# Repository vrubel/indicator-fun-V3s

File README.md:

# indicator-fun-V3s
Device "indicator.fun" implementation on the processor Allwinner V3s

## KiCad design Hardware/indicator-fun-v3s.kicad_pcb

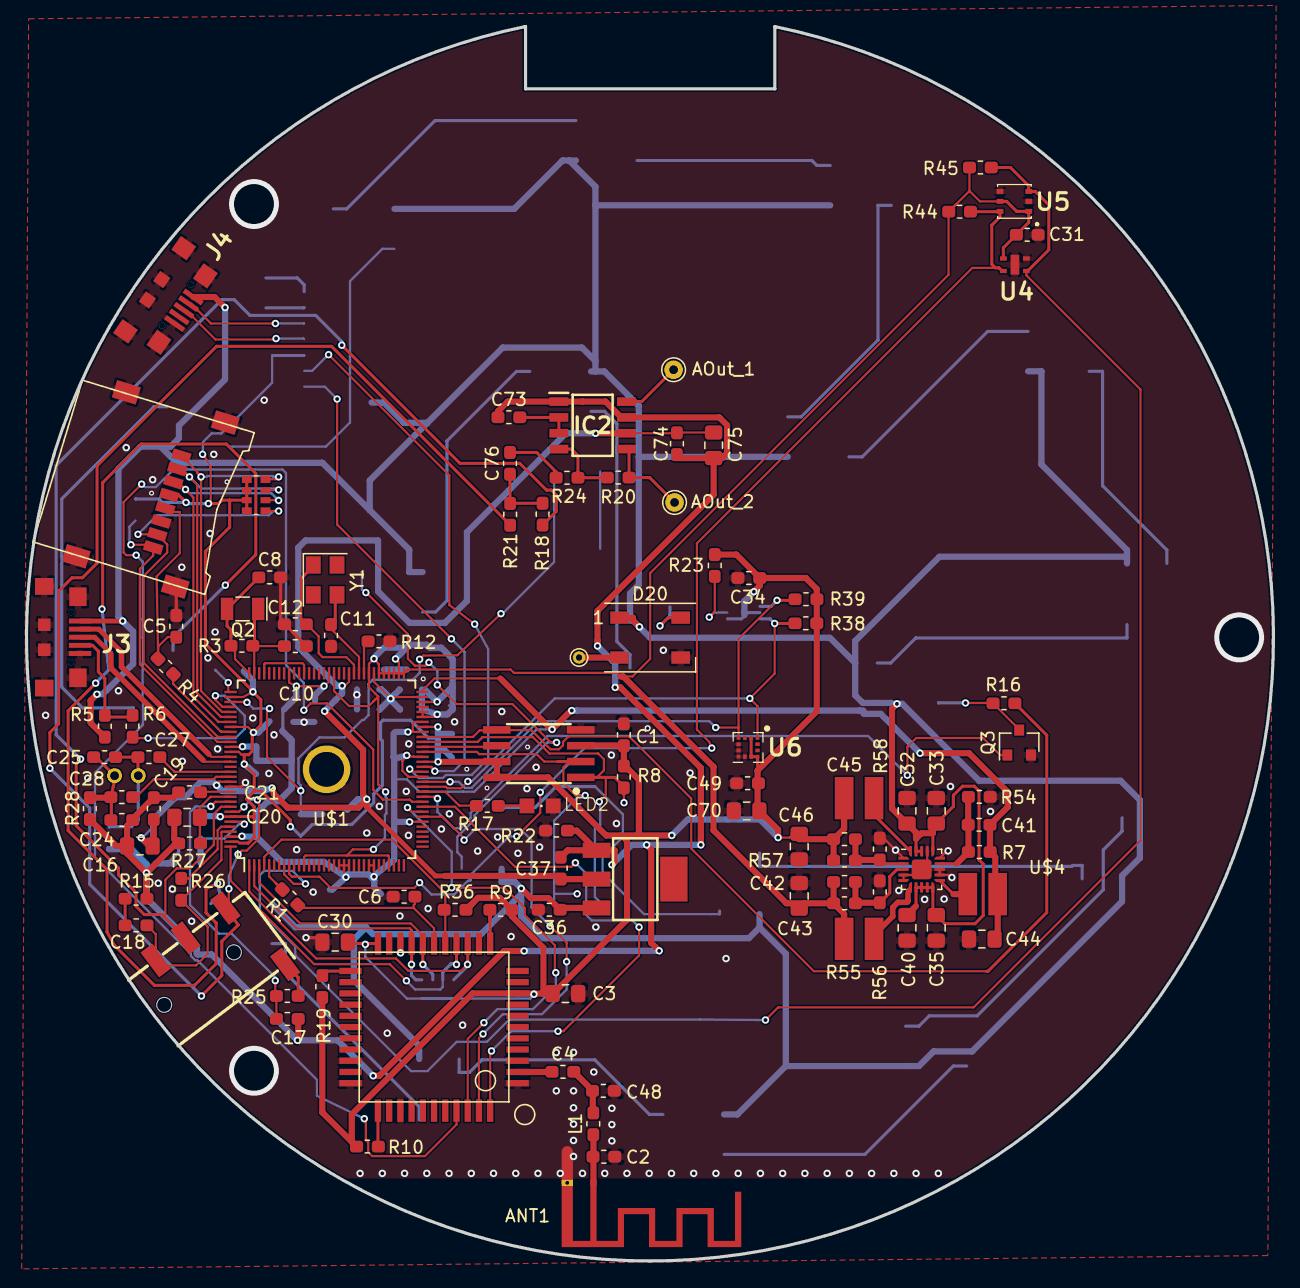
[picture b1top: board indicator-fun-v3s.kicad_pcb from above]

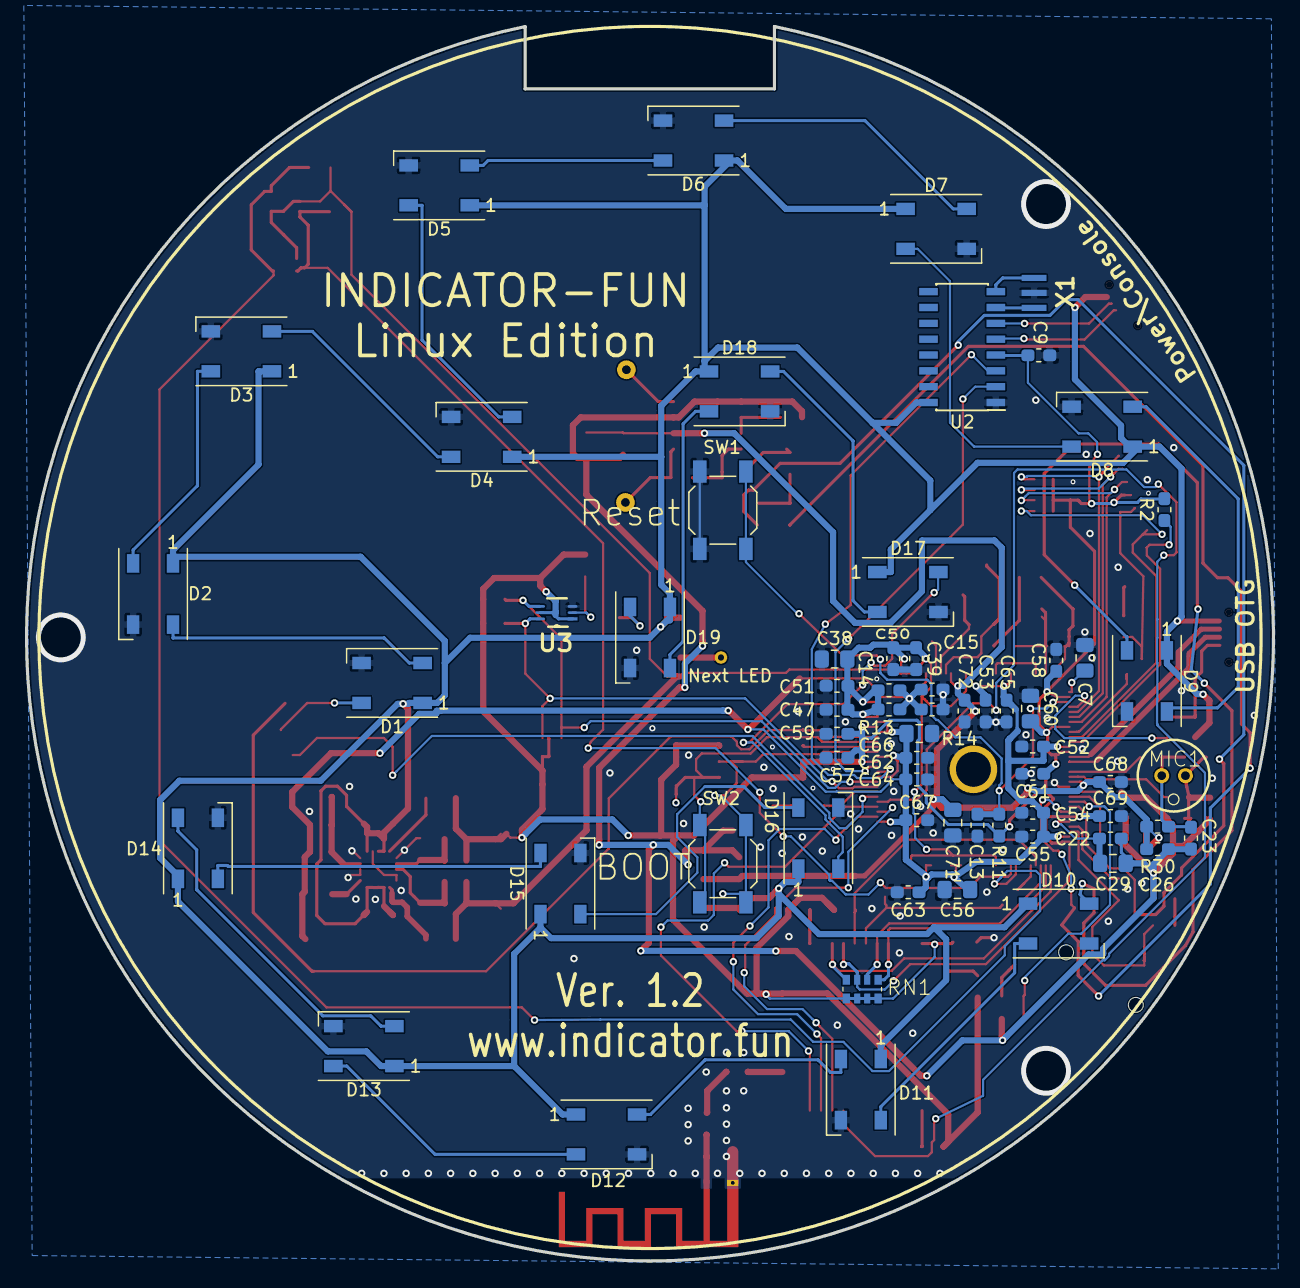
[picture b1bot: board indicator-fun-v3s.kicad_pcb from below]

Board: 2 copper layers, 100.0 x 99.0 mm, 168 parts (65 on the bottom side), 109 nets.

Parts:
ANT1: SWRA117D; Texas_SWRA117D_2.4GHz_Left
AOut_1: AOut_1; TestPoint_THTPad_D1.5mm_Drill0.7mm
AOut_2: AOut_2; TestPoint_THTPad_D1.5mm_Drill0.7mm
C1, C9, C14, C15, C18, C19, C22, C27, C28, C50, C51, C52, C53, C57, C58, C62, C63, C67, C68, C69, C72, C73, C74: 100nF; C_0603_1608Metric_Pad1.05x0.95mm_HandSolder
C2: 1pF; C_0603_1608Metric_Pad1.05x0.95mm_HandSolder
C3, C7, C16, C29, C30, C32, C33, C35, C38, C40, C43, C44, C46, C56, C60, C66, C71, C75: 10µF; C_0805_2012Metric_Pad1.15x1.40mm_HandSolder
C4: 10pF; C_0603_1608Metric_Pad1.05x0.95mm_HandSolder
C5, C6: 4.7pF; C_0603_1608Metric_Pad1.05x0.95mm_HandSolder
C8, C10, C11, C12, C41, C42, C45: 18pF; C_0603_1608Metric_Pad1.05x0.95mm_HandSolder
C13, C17, C21, C39, C47, C54, C55, C59, C61, C64, C65: 1µF; C_0603_1608Metric_Pad1.05x0.95mm_HandSolder
C20: 4.7µF; C_0805_2012Metric_Pad1.15x1.40mm_HandSolder
C23, C24, C26: 33pF; C_0603_1608Metric_Pad1.05x0.95mm_HandSolder
C25: 100pF; C_0603_1608Metric_Pad1.05x0.95mm_HandSolder
C31, C34, C49: 0.1uf; C_0603_1608Metric_Pad1.05x0.95mm_HandSolder
C36, C37: 100nf; C_0603_1608Metric_Pad1.05x0.95mm_HandSolder
C48: 1.2pF; C_0603_1608Metric_Pad1.05x0.95mm_HandSolder
C70: 22µF; C_0805_2012Metric_Pad1.15x1.40mm_HandSolder
C76: 0.22µF; C_0603_1608Metric_Pad1.05x0.95mm_HandSolder
D1, D2, D3, D4, D5, D6, D7, D8, D9, D10, D11, D12, D13, D14, D15, D16, D17, D18, D19, D20: WS2812B; LED_WS2812B_PLCC4_5.0x5.0mm_P3.2mm
IC1: LM1117; SOT223
IC2: MD8002A; SOIC127P600X175-8N
J1: TRANSFLASH-LOCK; TRANSFLASH-LOCK-SOCK
J2: AUDIO_JACK_SMD; AUDIO_JACK_3.5MM_TRRS_SMD_RA
J3: USB OTG; USB-B-Micro
J4: Power\Console; USB-B-Micro
L1: 2.2nH; L_0603_1608Metric_Pad1.05x0.95mm_HandSolder
L3, L4: 2,2µH; ODD-INDUCTOR
L5: 2.2µH; ODD-INDUCTOR
LED2: LEDCHIPLED_0805; CHIPLED_0805
MIC1: ELECTRET_MICROPHON-F6035AP; F6035AP
Q2: 32kHz; Crystal_SMD_MicroCrystal_CC7V-T1A-2Pin_3.2x1.5mm
Q3: BSS138; SOT-23
R1, R4: 33; R_0603_1608Metric_Pad1.05x0.95mm_HandSolder
R2, R11, R36: 47k; R_0603_1608Metric_Pad1.05x0.95mm_HandSolder
R3: 10M; R_0603_1608Metric_Pad1.05x0.95mm_HandSolder
R5, R9, R10, R56: 100k; R_0603_1608Metric_Pad1.05x0.95mm_HandSolder
R6, R17: 1k; R_0603_1608Metric_Pad1.05x0.95mm_HandSolder
R7, R54, R58: 150k; R_0603_1608Metric_Pad1.05x0.95mm_HandSolder
R8, R18, R19, R21, R38, R39, R44, R45: 10k; R_0603_1608Metric_Pad1.05x0.95mm_HandSolder
R12: 240 - 1%; R_0603_1608Metric_Pad1.05x0.95mm_HandSolder
R13, R14: 2k - 1%; R_0603_1608Metric_Pad1.05x0.95mm_HandSolder
R15: 22; R_0603_1608Metric_Pad1.05x0.95mm_HandSolder
R16: 300; R_0603_1608Metric_Pad1.05x0.95mm_HandSolder
R20: 68k; R_0603_1608Metric_Pad1.05x0.95mm_HandSolder
R22, R26: 0; R_0603_1608Metric_Pad1.05x0.95mm_HandSolder
R23: 10K; R_0603_1608Metric_Pad1.05x0.95mm_HandSolder
R24: 22k; R_0603_1608Metric_Pad1.05x0.95mm_HandSolder
R25, R28, R30: 2k; R_0603_1608Metric_Pad1.05x0.95mm_HandSolder
R27: 200k 1%; R_0603_1608Metric_Pad1.05x0.95mm_HandSolder
R55: 200k; R_0603_1608Metric_Pad1.05x0.95mm_HandSolder
R57: 680k; R_0603_1608Metric_Pad1.05x0.95mm_HandSolder
RN1, RN2: 4R-NEXB38V; EXB38V
SW1: Reset; SW_SPST_SKQG_WithoutStem
SW2: BOOT; SW_SPST_SKQG_WithoutStem
TP1: Next LED; TestPoint_THTPad_D1.0mm_Drill0.5mm
U1: 25F32006WSOI; SO08-EIAJ
U2: CH340G; SOIC-16_3.9x9.9mm_P1.27mm
U3: Rohm BH1730FVC-TR; SOP6_1
U4: Sensirion SHTC1; Sensirion-SHTC1
U5: SGP30
U6: LIS2DH12TR; LGA-12_1
U$1: V3S; LQFP-128_14x14mm_P0.4mm
U$2: RTL8723BS; LGA
U$4: EA3036; QFN-20-1EP_3x3mm_P0.45mm_EP1.6x1.6mm
X1: CSTCE12M0G52-R0
Y1: Crystal_GND24_Small; Crystal_SMD_SeikoEpson_FA238V-4Pin_3.2x2.5mm

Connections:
+1V2: C41.1, C44.2, C52.1, C53.1, C54.1, C55.1, C56.1, C62.1, C63.1, C64.1, C65.1, C66.1, C67.1, L3.P$1, R7.1, U$1.19, U$1.20, U$1.21, U$1.25, U$1.26, U$1.38, U$1.47, U$1.51, U$1.56, U$1.58, U$1.64, U$1.80, U$1.88, U$1.108, U$1.126
+1V8: C14.2, C31.1, C38.2, C39.1, C42.1, C43.2, C47.1, C50.1, C51.1, L4.P$1, R13.2, R44.1, R45.1, R55.1, U4.1, U5.1, U5.5, U$1.12, U$1.29, U$1.59, U$1.60, U$1.61, U$1.62, U$1.65, U$1.66, U$1.67, U$1.68, U$1.69, U$1.70, U$1.72, U$1.79
+3V3: C1.1, C3.1, C9.1, C30.1, C34.1, C45.1, C46.2, C49.2, C57.1, C58.1, C59.1, C60.1, C61.1, C69.1, C70.2, J1.4, L5.P$1, R2.2, R8.2, R9.1, R10.2, R11.2, R19.2, R23.1, R36.1, R38.1, R39.1, R57.1, RN1.1, RN1.2, RN1.3, RN1.4, RN2.1, RN2.2, RN2.3, RN2.4, U1.3, U1.7, U1.8, U2.4, U3.1, U3.5, U6.2, U6.9, U6.10, U$1.50, U$1.57, U$1.98, U$1.104, U$1.109, U$1.122, U$1.127, U$2.P$9, U$2.P$22
+3V3A: C16.2, C19.2, C26.2, C37.1, C68.1, C71.1, C72.1, C74.1, C75.2, IC1.2, IC2.6, R30.2, U$1.76, U$1.115
+5V: C32.1, C33.1, C35.1, C36.1, C40.1, D1.1, D2.1, D3.1, D4.1, D5.1, D6.1, D7.1, D8.1, D9.1, D10.1, D11.1, D12.1, D13.1, D14.1, D15.1, D16.1, D17.1, D18.1, D19.1, D20.1, IC1.3, J3.1, J4.1, R5.2, U2.16, U$4.7, U$4.8, U$4.9, U$4.10, U$4.16, U$4.18, U$4.19
/Power/SVREF: C14.1, C15.2, R13.1, R14.2, U$1.63, U$1.71
/Power/for_delete: U$1.85, U$1.93
/Power/x24min: C12.2, U$1.75, Y1.1
/Power/x24mount: C11.2, U$1.74, Y1.3
/Power/x32kin: C8.1, Q2.2, R3.2, U$1.96
/Power/x32kout: C10.1, Q2.1, R3.1, U$1.95
/Sensors/Light-Int: R23.2, U3.2
/USB-SDC0-Audio/HP_COM: C18.2, J2.RING2, R26.2, U$1.125
/USB-SDC0-Audio/HP_COMFB: R26.1, U$1.124
/USB-SDC0-Audio/HP_L: J2.TIP, R21.1, U$1.121
/USB-SDC0-Audio/HP_R: J2.RING1, R18.1, U$1.120
/USB-SDC0-Audio/MICIN1N: C28.1, U$1.114
/USB-SDC0-Audio/MICIN1P: C27.1, U$1.113
/USB-SDC0-Audio/MIC_HBIAS: C17.1, R25.2, U$1.119
/USB-SDC0-Audio/USB_D+: J3.3, U$1.111
/USB-SDC0-Audio/USB_D-: J3.2, U$1.110
/USB-SDC0-Audio/VRA1: C21.2, U$1.117
/USB-SDC0-Audio/VRA2: C20.2, R27.2, U$1.118
/WLAN/SDC1/CLK: C6.1, R1.1, U$2.P$17
/WLAN/SDC1/CMD: R36.2, U$1.4, U$2.P$16
/WLAN/SDC1/D0: RN1.6, U$1.3, U$2.P$18
/WLAN/SDC1/D1: RN1.5, U$1.2, U$2.P$19
/WLAN/SDC1/D2: RN1.8, U$1.1, U$2.P$14
/WLAN/SDC1/D3: RN1.7, U$1.128, U$2.P$15
/WLAN/SPI1/CS: R8.1, SW2.3, SW2.4, U1.1, U$1.54
/WLAN/SPI1/MISO: SW2.1, SW2.2, U1.2, U$1.52
/WLAN/SPI1/SCK: U1.6, U$1.53
/WLAN/UART2/CTS/PB3: U$1.42, U$2.P$41
/WLAN/UART2/RTS/PB2: U$1.41, U$2.P$44
/WLAN/UART2/RX/PB1: U$1.40, U$2.P$42
/WLAN/UART2/TX/PB0: U$1.39, U$2.P$43
AGND: C16.1, C17.2, C19.1, C20.1, C21.1, C22.2, C23.1, C24.1, C26.1, C29.1, C37.2, C73.1, C74.2, C75.1, IC1.1, IC2.1, IC2.7, R15.1, R22.1, R27.1, R28.2
CS2: Q3.1, U$1.43
GND: ANT1.2, C1.2, C2.1, C3.2, C5.2, C6.2, C7.2, C8.2, C9.2, C10.2, C11.1, C12.1, C13.2, C15.1, C30.2, C31.2, C32.2, C33.2, C34.2, C35.2, C36.2, C38.1, C39.2, C40.2, C43.1, C44.1, C46.1, C47.2, C48.1, C49.1, C50.2, C51.2, C52.2, C53.2, C54.2, C55.2, C56.2, C57.2, C58.2, C59.2, C60.2, C61.2, C62.2, C63.2, C64.2, C65.2, C66.2, C67.2, C68.2, C69.2, C70.1, C71.2, C72.2, D1.3, D2.3, D3.3, D4.3, D5.3, D6.3, D7.3, D8.3, D9.3, D10.3, D11.3, D12.3, D13.3, D14.3, D15.3, D16.3, D17.3, D18.3, D19.3, D20.3, J1.6, J1.S1, J1.S2, J1.S3, J1.S4, J3.5, J4.5, LED2.C, Q3.2, R12.2, R14.1, R22.2, R54.1, R56.1, R58.1, SW1.1, SW1.2, U1.4, U2.1, U3.3, U4.4, U4.5, U5.2, U5.4, U6.5, U6.6, U6.7, U6.8, U$1.116, U$1.P$1, U$2.P$1, U$2.P$3, U$2.P$20, U$2.P$31, U$2.P$33, U$2.P$36, U$4.1, U$4.4, U$4.5, U$4.12, U$4.13, U$4.15, U$4.17, U$4.21, X1.2
LED_CTL: R16.1, U1.5, U$1.55
unnamed: ANT1.1, C2.2, L1.1
unnamed: AOut_1.1, IC2.8
unnamed: AOut_2.1, IC2.5, R20.2
unnamed: C4.1, U$2.P$2
unnamed: C4.2, C48.2, L1.2
unnamed: C7.1, U$1.97
unnamed: C13.1, R11.1, SW1.3, SW1.4, U$1.99
unnamed: C18.1, R15.2
unnamed: C22.1, C29.2, U$1.123
unnamed: C23.2, C25.2, C27.2, MIC1.2, R30.1
unnamed: C24.2, C25.1, C28.2, MIC1.1, R28.1
unnamed: C41.2, R7.2, R54.2, U$4.14
unnamed: C42.2, R55.2, R56.2, U$4.3
unnamed: C45.2, R57.2, R58.2, U$4.2
unnamed: C73.2, IC2.2, IC2.3
unnamed: C76.1, R18.2, R21.2
unnamed: C76.2, R24.1
unnamed: D1.2, D2.4
unnamed: D1.4, Q3.3, R16.2
unnamed: D2.2, D3.4
unnamed: D3.2, D4.4
unnamed: D4.2, D5.4
unnamed: D5.2, D6.4
unnamed: D6.2, D7.4
unnamed: D7.2, D8.4
unnamed: D8.2, D9.4
unnamed: D10.2, D11.4
unnamed: D9.2, D10.4
unnamed: D11.2, D12.4
unnamed: D12.2, D13.4
unnamed: D13.2, D14.4
unnamed: D14.2, D15.4
unnamed: D15.2, D16.4
unnamed: D16.2, D17.4
unnamed: D17.2, D18.4
unnamed: D18.2, D19.4
unnamed: D19.2, D20.4
unnamed: D20.2, TP1.1
unnamed: IC2.4, R20.1, R24.2
unnamed: J2.EARTH, R25.1
unnamed: J3.4, R5.1, R6.1
unnamed: J4.2, U2.6
unnamed: J4.3, U2.5
unnamed: L3.P$2, U$4.11
unnamed: L4.P$2, U$4.6
unnamed: L5.P$2, U$4.20
unnamed: LED2.A, R17.1
unnamed: R1.2, U$1.5
unnamed: R4.2, U$1.105
unnamed: R9.2, U$2.P$12
unnamed: R10.1, U$2.P$34
unnamed: R12.1, U$1.73
unnamed: R19.1, U$2.P$23
unnamed: U2.7, X1.1
unnamed: U2.8, X1.3
PWM1_SYSLED: R17.2, U$1.44
SCL: R38.2, U3.6, U6.1, U$1.45
SCL-1.8: R44.2, U4.2, U5.6, U$1.9
SDA: R39.2, U3.4, U6.4, U$1.46
SDA-1.8: R45.2, U4.3, U5.3, U$1.8
SDC0/CLK: C5.1, J1.5, R4.1
SDC0/CMD: J1.3, RN2.6, U$1.103
SDC0/D0: J1.7, RN2.5, U$1.106
SDC0/D1: J1.8, R2.1, U$1.107
SDC0/D2: J1.1, RN2.8, U$1.101
SDC0/D3: J1.2, RN2.7, U$1.102
UART0/RX: U2.2, U$1.49
UART0/TX: U2.3, U$1.48
USB/ID: R6.2, U$1.100

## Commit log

2019-05-16 ver 1.0 Operable device
2019-05-16 Added a photo of the assembled PCB
2019-06-02 SPI подсоединен к цепочке светодиодов и установлен транзистор разрешающий управление цепочкой по CS2
2019-06-02 Заменены кварцы
2019-06-06 Версия 1.1 Отправлена в производство
2019-10-26 Переход на новую версию KiCad
2019-10-26 Новые картинки
2019-11-24 Добавлен усилитель, но не сделана трассировка дорожек
2019-11-24 Разведены две дорожки звука на усилитель
2019-11-24 Разведена шина AGND
2019-11-24 Добавлен вырез под динамик
2020-03-29 Добавлена html страница InteractiveHtmlBom для версии 1.2
